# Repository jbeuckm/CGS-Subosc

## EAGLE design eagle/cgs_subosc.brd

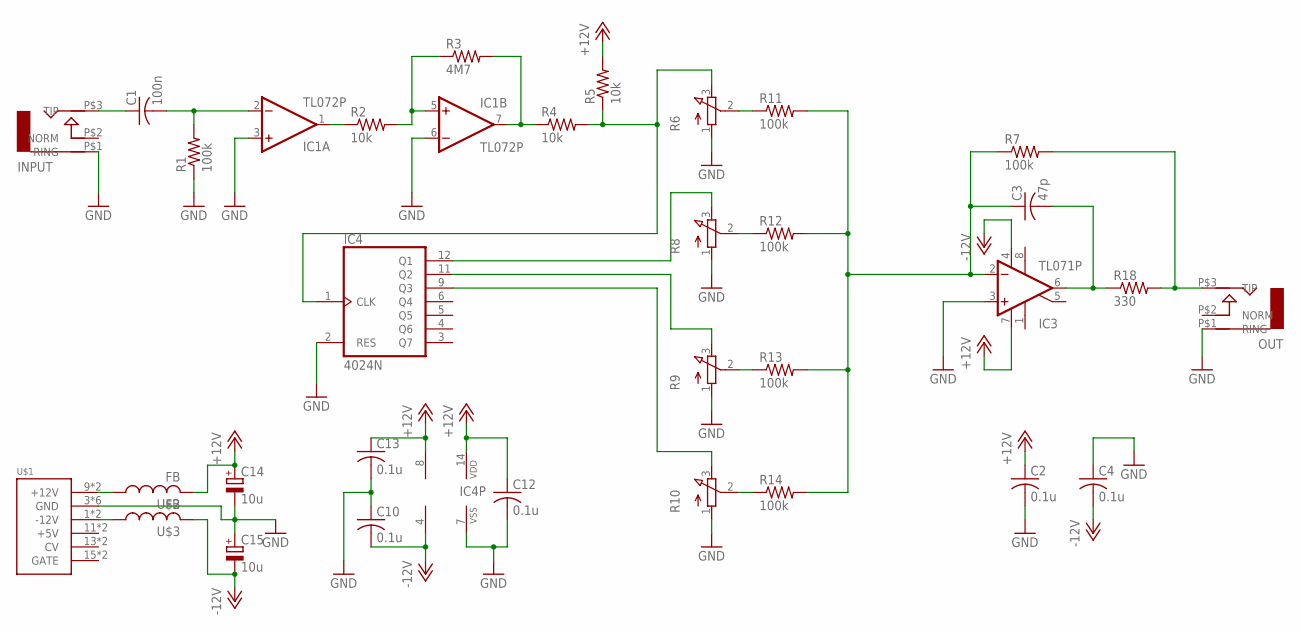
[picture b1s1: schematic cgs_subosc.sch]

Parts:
C1: 100n; C050-050X075
C2, C4, C10, C12, C13: 0.1u; C025-030X050
C3: 47p; C050-050X075
C14, C15: 10u; B45181A
IC1: TL072P; DIL08
IC3: TL071P; DIL08
IC4: 4024N; DIL14
INPUT: AUDIO-JACK; ERTHENVAR-JACK-90DEG
OUT: AUDIO-JACK; ERTHENVAR-JACK-90DEG
R1, R7, R11, R12, R13, R14: 100k; 0207/10
R2, R4, R5: 10k; 0207/10
R3: 4M7; 0207/10
R6, R8, R9, R10: 3RP/1610N
R18: 330; 0207/10
U$1: POWER; POWER_16
U$2, U$3: FB

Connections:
+12V: C2.1, C12.1, C13.1, C14.+, IC1.8 (V+), IC3.7 (V+), IC4.14 (VDD), R5.2, U$2.P$2 (2)
-12V: C4.2, C10.2, C15.-, IC1.4 (V-), IC3.4 (V-), U$3.P$2 (2)
GND: C2.2, C4.1, C10.1, C12.2, C13.2, C14.-, C15.+, IC1.3 (+IN), IC1.6 (-IN), IC3.3 (+IN), IC4.2 (RES), IC4.7 (VSS), INPUT.P$1 (RING), OUT.P$1 (RING), R1.1, R6.1 (A), R8.1 (A), R9.1 (A), R10.1 (A), U$1.3 (GND), U$1.4 (GND), U$1.5 (GND), U$1.6 (GND), U$1.7 (GND), U$1.8 (GND)
unnamed: C1.1, INPUT.P$3 (TIP)
unnamed: C1.2, IC1.2 (-IN), R1.2
unnamed: IC1.5 (+IN), R2.2, R3.1
unnamed: C3.1, IC3.2 (-IN), R7.1, R11.2, R12.2, R13.2, R14.2
unnamed: IC1.7 (OUT), R3.2, R4.1
unnamed: IC1.1 (OUT), R2.1
unnamed: C3.2, IC3.6 (OUT), R18.1
unnamed: OUT.P$3 (TIP), R7.2, R18.2
unnamed: IC4.1 (CLK), R4.2, R5.1, R6.3 (E)
unnamed: R6.2 (S), R11.1
unnamed: R8.2 (S), R12.1
unnamed: R9.2 (S), R13.1
unnamed: R10.2 (S), R14.1
unnamed: IC4.12 (Q1), R8.3 (E)
unnamed: IC4.11 (Q2), R9.3 (E)
unnamed: IC4.9 (Q3), R10.3 (E)
unnamed: U$1.9 (+12V), U$1.10 (+12V), U$2.P$1 (1)
unnamed: U$1.1 (-12V), U$1.2 (-12V), U$3.P$1 (1)

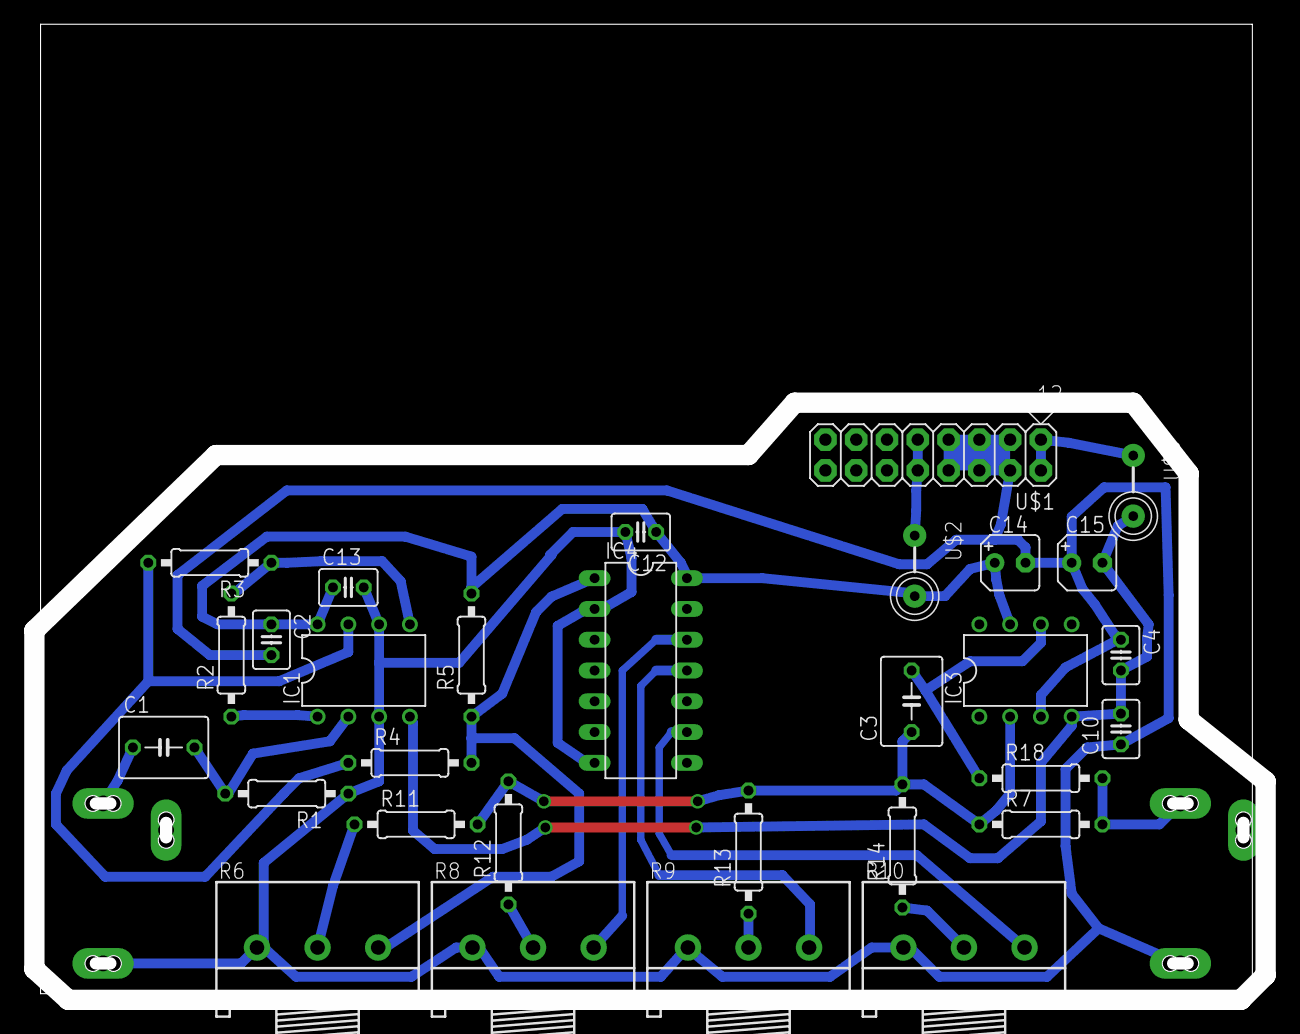
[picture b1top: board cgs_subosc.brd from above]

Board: 2 copper layers, 101.6 x 80.5 mm, 32 parts (0 on the bottom side), 21 nets.

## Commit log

2015-12-29 verified then scrunched a little
2015-12-30 layout image
2015-12-30 panel
